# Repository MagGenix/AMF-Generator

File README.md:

# AMF Generator

A digitally controlled push-pull converter designed for generation of an alternating magnetic field (AMF). THIS DESIGN IS INCOMPLETE. Design specifications had included an operating frequency of 10-1000 kHz, output currents between 0-10A, and a system operating voltage of 12V.

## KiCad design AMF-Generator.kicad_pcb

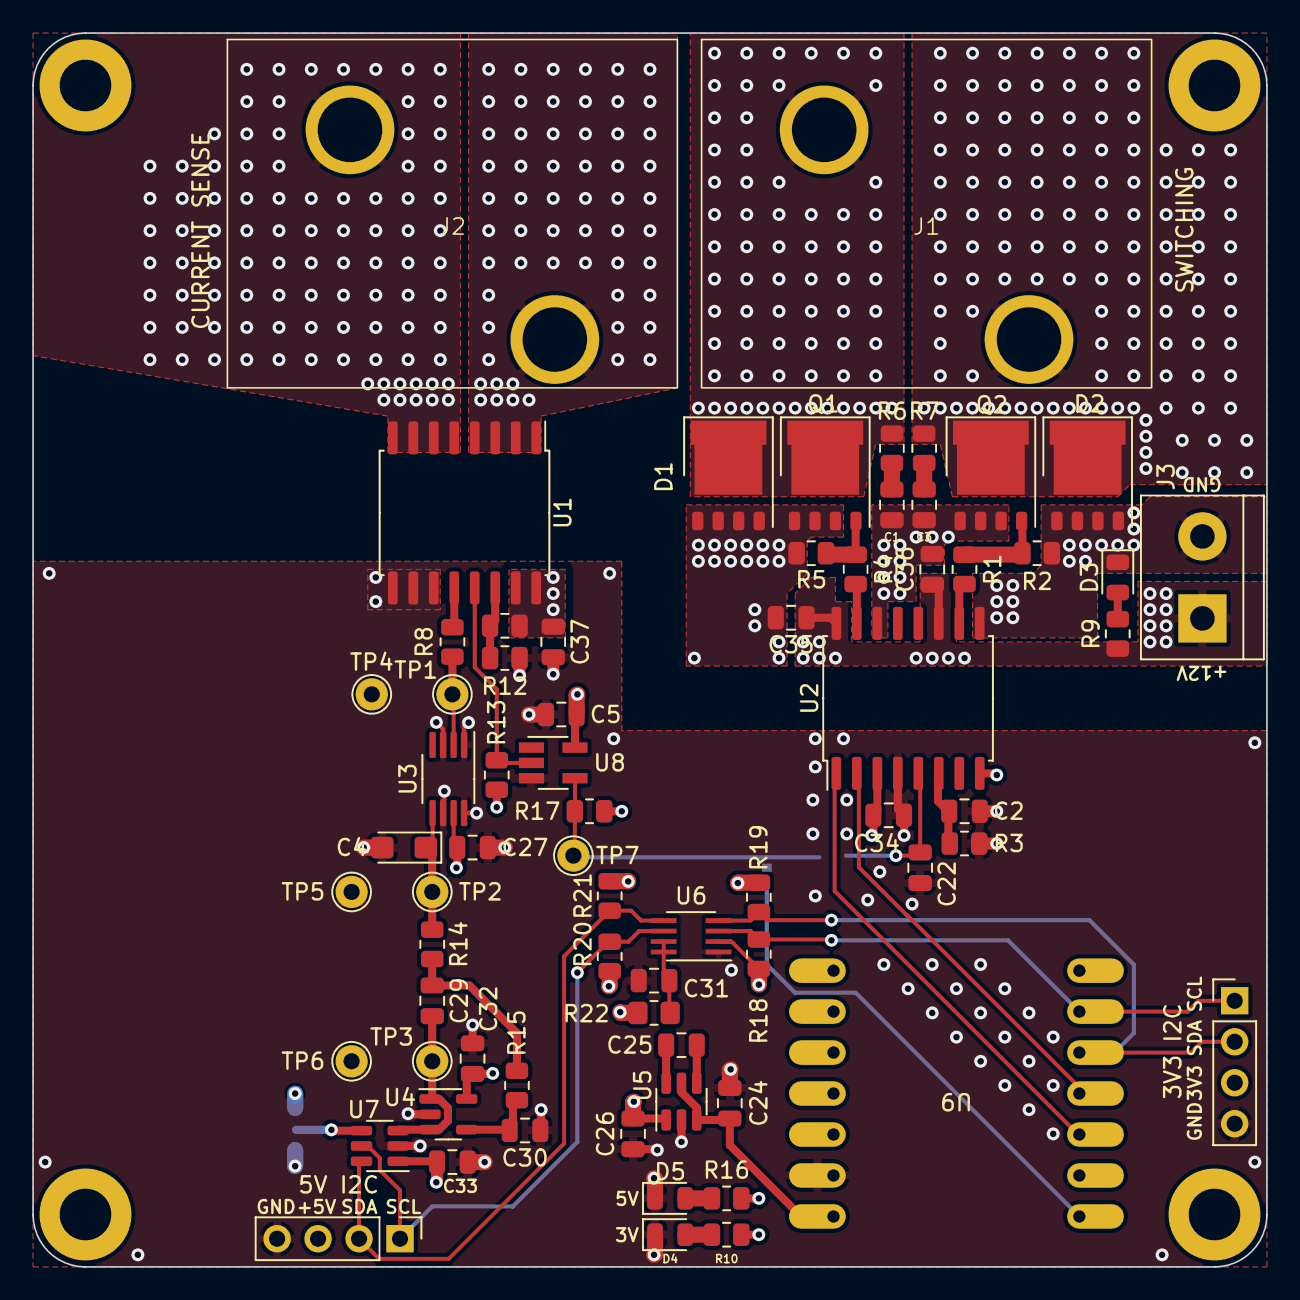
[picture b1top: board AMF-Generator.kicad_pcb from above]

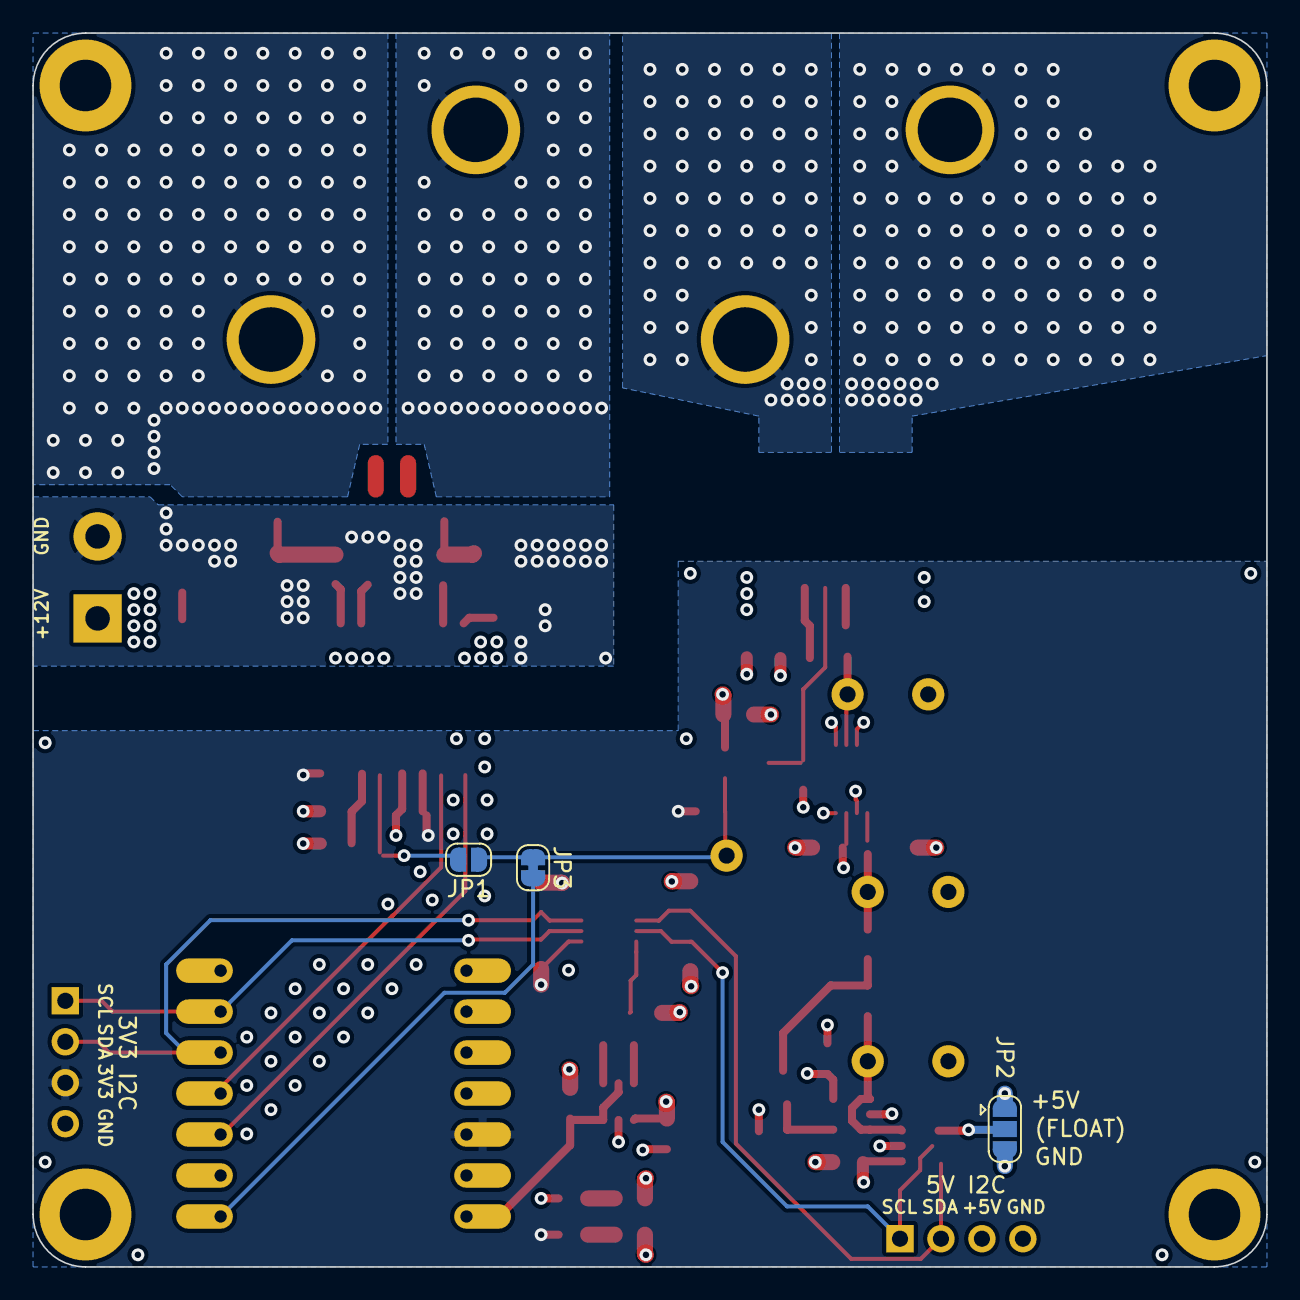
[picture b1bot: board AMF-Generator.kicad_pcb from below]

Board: 4 copper layers, 76.5 x 76.5 mm, 76 parts (3 on the bottom side), 41 nets.

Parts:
C1, C3, C5, C31, C32, C33, C34, C37: 0.1uF; C_0805_2012Metric
C2: 2.2nF; C_0805_2012Metric
C4: 10uF; CP_EIA-3216-18_Kemet-A
C22: 1nF; C_0805_2012Metric
C24, C25, C26, C30, C35, C36: 1uF; C_0805_2012Metric
C27: 10nF; C_0805_2012Metric
C29: 10uF; C_0805_2012Metric
D1, D2: V30K45; PQFN-8-EP_6x5mm_P1.27mm_Generic
D3, D4, D5: LED; LED_0805_2012Metric
H1, H2, H3, H4: MountingHole; MountingHole_3.2mm_M3_ISO7380_Pad
J1: SW_OUT; 0389690002
J2: CUR_SENSE; 0389690002
J3: PWR_IN; TerminalBlock_bornier-2_P5.08mm
J4: I2C_5V; PinHeader_1x04_P2.54mm_Vertical
J5: I2C_3V3; PinHeader_1x04_P2.54mm_Vertical
JP1: Driver-Disable; SolderJumper-2_P1.3mm_Open_RoundedPad1.0x1.5mm
JP2: ADDR_JUMPER; SolderJumper-3_P1.3mm_Open_RoundedPad1.0x1.5mm
JP3: MCU_Disable; SolderJumper-2_P1.3mm_Bridged_RoundedPad1.0x1.5mm
Q1, Q2: ISC012N04LM6ATMA1; PQFN-8-EP_6x5mm_P1.27mm_Generic
R1, R4: 4.7; R_0805_2012Metric
R2, R5: 100; R_0805_2012Metric
R3, R6, R7, R12, R13, R17: 1K; R_0805_2012Metric
R8: 0; R_0805_2012Metric
R9: 2K; R_0805_2012Metric
R10: 260; R_0805_2012Metric
R11: 3.3K; R_0805_2012Metric
R14, R18, R19, R20, R21: 5.6K; R_0805_2012Metric
R15: 24.9K; R_0805_2012Metric
R16: 600; R_0805_2012Metric
R22: 200K; R_0805_2012Metric_Pad1.20x1.40mm_HandSolder
TP1, TP2, TP3, TP4, TP5, TP6, TP7: TestPoint; TestPoint_THTPad_D2.0mm_Drill1.0mm
U1: ACS732KLATR-75AB; SOIC-16W_7.5x10.3mm_P1.27mm
U2: UCC21540; SOIC-16W_7.5x10.3mm_P1.27mm
U3: LTC1968; MSOP-8_3x3mm_P0.65mm
U4: LT1880; TSOT-23-5
U5: CAT3200-5; SOT-23-6
U6: LSF0102; SSOP-8_2.95x2.8mm_P0.65mm
U7: ADC101C027CIMK; SOT-23-6
U8: 74LVC1G06; SOT-23-5_HandSoldering
U9: QTPY; QTPY-RP2040

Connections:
+3V3: C34.1, J5.3, R10.1, R17.1, R18.2, R19.2, U2.3 (VCCI), U2.8 (VCCI), U6.2 (VREF_A), U9.10 (3.3V)
+5V: C5.1, C26.1, C27.1, C32.1, C33.1, C37.1, J4.3, JP2.1 (A), R11.1, R13.1, R16.1, R20.2, R21.2, R22.1, U1.15 (VCC), U1.16 (VCC), U3.7 (V+), U4.5 (V+), U5.1 (VOUT), U7.1 (V_{A}), U8.5 (VCC)
+12V: C35.1, C36.1, J3.1, R9.1, U2.11 (VDDB), U2.16 (VDDA)
AC_A: J2.2, U1.1 (IP+), U1.2 (IP+), U1.3 (IP+), U1.4 (IP+)
AC_B: J2.1, U1.5 (IP-), U1.6 (IP-), U1.7 (IP-), U1.8 (IP-)
FAULT: JP1.1 (A), JP3.1 (A), R17.2, TP7.1, U8.4
GND: C2.2, C4.2, C5.2, C22.2, C24.2, C26.2, C27.2, C30.2, C31.2, C32.2, C33.2, C34.2, C37.2, D4.1 (K), D5.1 (K), J4.4, J5.4, JP2.3 (B), R3.2, R12.1, TP4.1, TP5.1, TP6.1, U1.9 (GND), U1.10 (GND), U1.11 (PROGRAM), U2.4 (GND), U3.1 (GND), U3.3 (IN2), U3.6 (OUT_RTN), U3.8 (EN), U4.2 (V-), U5.2 (GND), U6.1 (GND), U7.2 (GND), U8.3 (GND), U9.9 (GND)
GNDPWR: C1.2, C3.2, C35.2, C36.2, D1.1, D1.2, D1.3, D1.4, D2.1, D2.2, D2.3, D2.4, D3.1 (K), J3.2, Q1.1 (S), Q1.2 (S), Q1.3 (S), Q2.1 (S), Q2.2 (S), Q2.3 (S), R2.2, R5.2, U2.9 (VSSB), U2.14 (VSSA)
unnamed: C1.1, R6.2
unnamed: C3.1, R7.2
unnamed: C29.1, R14.2, R15.1
unnamed: D3.2 (A), R9.2
unnamed: D4.2 (A), R10.2
unnamed: D5.2 (A), R16.2
unnamed: C22.1, JP1.2 (B), U2.5 (DIS)
unnamed: JP2.2 (C), U7.4 (ADDR)
unnamed: JP3.2 (B), U9.1 (A0)
unnamed: Q1.4 (G), R4.2, R5.1
unnamed: Q2.4 (G), R1.2, R2.1
unnamed: R11.2, R12.2, U1.14 (VOC)
unnamed: R13.2, U1.13 (~FAULT), U8.2
unnamed: C2.1, R3.1, U2.6 (DT)
unnamed: R4.1, U2.15 (OUTA)
unnamed: R1.1, U2.10 (OUTB)
unnamed: R8.2, TP1.1, U3.2 (IN1)
unnamed: C4.1, R14.1, TP2.1, U3.5 (VOUT)
unnamed: C29.2, TP3.1, U4.1 (OUT), U4.3 (+IN), U7.3 (V_{IN})
unnamed: C30.1, R15.2, U4.4 (-IN)
unnamed: C25.2, U5.4 (CNEG)
unnamed: C25.1, U5.6 (CPOS)
unnamed: C24.1, U5.3 (~SHDN), U5.5 (VIN), U9.8 (5V)
unnamed: C31.1, R22.2, U6.7 (VREF_B), U6.8 (EN)
PWM_A: U2.1 (INA), U9.3 (A2)
PWM_B: U2.2 (INB), U9.4 (A3)
SCL_3V3: J5.1, R18.1, U6.3 (A1), U9.6 (SCL)
SCL_5: J4.1, R20.1, U6.6 (B1), U7.5 (SCL)
SDA_3V3: J5.2, R19.1, U6.4 (A2), U9.5 (SDA)
SDA_5: J4.2, R21.1, U6.5 (B2), U7.6 (SDA)
SENSE_AC: R8.1, U1.12 (VIOUT)
SW_A: D1.5, J1.1, Q1.5 (D), R6.1
SW_B: D2.5, J1.2, Q2.5 (D), R7.1

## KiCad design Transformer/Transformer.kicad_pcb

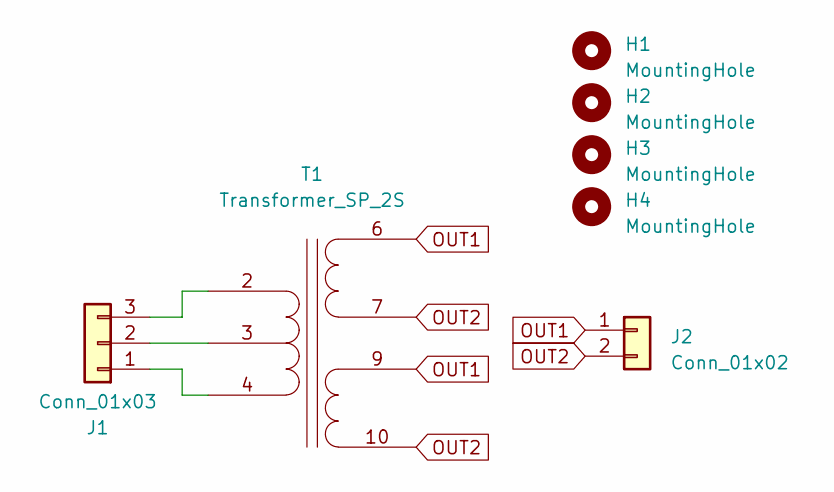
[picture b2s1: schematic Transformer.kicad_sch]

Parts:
H1, H2, H3, H4: MountingHole; MountingHole_3.2mm_M3_ISO7380_Pad
J1: Conn_01x03; 0389690003
J2: Conn_01x02; 0389690002
T1: Transformer_SP_2S; Transformer_Coilcraft_PL140

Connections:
unnamed: J1.1, T1.4 (IN-)
unnamed: J1.2, T1.3 (PM)
unnamed: J1.3, T1.2 (IN+)
OUT1: J2.1, T1.6 (OUT1A), T1.9 (OUT2A)
OUT2: J2.2, T1.7 (OUT1B), T1.10 (OUT2B)

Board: 4 copper layers, 7 parts (0 on the bottom side), 5 nets, no tracks yet.

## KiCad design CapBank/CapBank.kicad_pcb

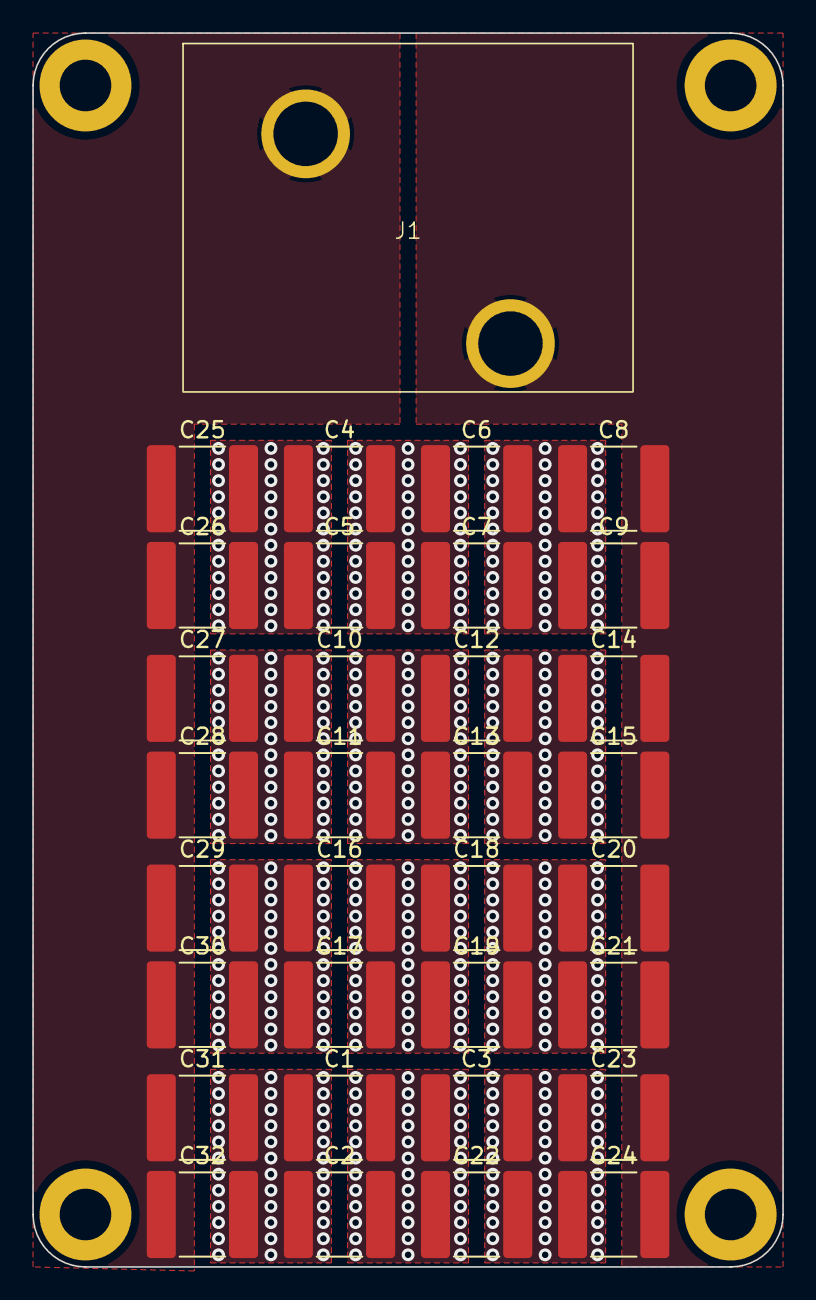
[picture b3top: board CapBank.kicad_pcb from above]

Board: 2 copper layers, 46.5 x 76.5 mm, 37 parts (0 on the bottom side), 14 nets, no tracks yet.

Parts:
C1, C3, C4, C6, C8, C10, C12, C14, C16, C18, C20, C23, C25, C27, C29, C31: 8200p; C_2220_5650Metric
C2, C5, C7, C9, C11, C13, C15, C17, C19, C21, C22, C24, C26, C28, C30, C32: 6800p; C_2220_5650Metric
H1, H2, H3, H4: MountingHole; MountingHole_3.2mm_M3_ISO7380_Pad
J1: CONN; 0389690002

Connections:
unnamed: C1.1, C2.1, C31.2, C32.2
unnamed: C1.2, C2.2, C3.1, C22.1
unnamed: C4.2, C5.2, C6.1, C7.1
unnamed: C6.2, C7.2, C8.1, C9.1
unnamed: C10.1, C11.1, C27.2, C28.2
unnamed: C10.2, C11.2, C12.1, C13.1
unnamed: C12.2, C13.2, C14.1, C15.1
unnamed: C16.1, C17.1, C29.2, C30.2
unnamed: C16.2, C17.2, C18.1, C19.1
unnamed: C18.2, C19.2, C20.1, C21.1
unnamed: C3.2, C22.2, C23.1, C24.1
unnamed: C4.1, C5.1, C25.2, C26.2
unnamed: C25.1, C26.1, C27.1, C28.1, C29.1, C30.1, C31.1, C32.1, J1.1
unnamed: C8.2, C9.2, C14.2, C15.2, C20.2, C21.2, C23.2, C24.2, J1.2

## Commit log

2023-06-30 Schematic almost complete
2023-06-30 Basically done with schematic, will split to different PCBs now
2023-07-01 Finished footprint assignment
2023-07-01 Added a couple notes
2023-07-01 Switching from Feather to XIAO / QtPy to save on board space
2023-07-01 Initial pass of component placement complete. Added test points and i2c headers, also changed 12V input to terminal block
2023-07-01 grouped some elements
2023-07-03 initial pass of layout complete
2023-07-03 Cleanup, changed board outline, DRC errors resolved
2023-07-03 More warnings resolved
2023-07-03 Lots of vias
2023-07-03 adding useful labels
2023-07-03 More labels and cleanup
2023-07-03 Updated with selectable I2C addresses
2023-07-04 Fix schematic issues (incl QTPY symbol) and some board cleanup
2023-07-04 misc changes
2023-07-05 Added bypass cap to inverter and some cleanup
2023-07-05 Update to improved barrier block and cap bank pcb nearly done
2023-07-06 cleanup
2023-07-06 Changes to cap bank WIP
2023-07-06 Cap bank updated. Vias still WIP
2023-07-07 Added transformer pcb
2023-07-07 made dimensions multiples of 10 mm
2023-11-24 Add LTC6904 for clock generation
2023-12-11 Level shifter now obsolete, change to TI part
2023-12-11 Layout updated. Silk still WIP
2023-12-11 fix silk
2025-01-27 Adding LICENSE
2025-01-27 removed module
2025-01-27 Edit gitignore
2025-01-27 Adding README
